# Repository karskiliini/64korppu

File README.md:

# 64korppu

Standardi PC:n 1.44MB 3.5" HD-korppuasema Commodore 64 -tietokoneeseen. FAT12-levyformaatti mahdollistaa tiedostojen siirron C64:n ja PC:n välillä.

## Vaihtoehdot

| # | Ratkaisu | Liitäntä | Hinta | RAM | Tasonmuuntimet | Suositus |
|---|---|---|---|---|---|---|
| **[A](docs/A-IEC-Pico/)** | **IEC + Raspberry Pi Pico** | IEC-sarjaväylä | ~12€ | 264 KB | 4x BSS138 | **Suositeltu** |
| [B](docs/B-Expansion-FDC/) | Expansion port + FDC-piiri | Expansion port | ~20-30€ | - | Ei | Nopein |
| [C](docs/C-Userport-Pico/) | User port + Raspberry Pi Pico | User port | ~12€ | 264 KB | 1x 74LVC245 + 2x BSS138 | Kompromissi |
| [D](docs/D-IEC-Nano/) | IEC + Arduino Nano | IEC-sarjaväylä | ~8€ | 2 KB | **Ei yhtään** | Halvin |
| [E](docs/E-IEC-Nano-SRAM/) | IEC + Arduino Nano + SPI SRAM | IEC-sarjaväylä | ~10-13€ | 2+128 KB | **Ei yhtään** | Nano tehostettuna |

## Arkkitehtuuri

```
C64 ──[IEC / User port / Expansion port]──> Ohjain ──[34-pin]──> PC 3.5" HD floppy
                                                         │
                                                    FAT12-levy
                                                    (1.44 MB)
                                                         │
                                                    PC lukee/kirjoittaa
                                                    samaa levyä
```

## Miksi?

- **Tiedostonsiirto** C64:n ja modernin PC:n välillä ilman erikoislaitteita
- **FAT12** on universaali — levy toimii molemmissa koneissa
- **.PRG-tiedostot** tallennetaan suoraan levylle (2 tavun load address + data)
- **.D64 disk imaget** tuettuja — kopioi .D64-tiedosto levylle, mounttaa C64:llä, lataa ohjelmia suoraan
- C64:llä: `LOAD "PELI.PRG",8` / `SAVE "OMA.PRG",8` / `LOAD "$",8`

## Projektin rakenne

```
64korppu/
├── docs/
│   ├── A-IEC-Pico/           Vaihtoehto A: IEC + Pico (suositeltu)
│   │   ├── README.md         Yhteenveto
│   │   ├── kuvaus.md         Arkkitehtuuri ja komponentit
│   │   ├── piirikaavio.md    Yksityiskohtainen piirikaavio
│   │   └── d64-tuki.md       D64 disk image -tuki
│   ├── B-Expansion-FDC/      Vaihtoehto B: Expansion port + FDC
│   │   ├── README.md
│   │   ├── kuvaus.md
│   │   └── piirikaavio.md
│   ├── C-Userport-Pico/      Vaihtoehto C: User port + Pico
│   │   ├── README.md
│   │   ├── kuvaus.md
│   │   └── piirikaavio.md
│   ├── D-IEC-Nano/           Vaihtoehto D: IEC + Arduino Nano
│   │   ├── README.md
│   │   ├── kuvaus.md
│   │   └── piirikaavio.md
│   └── E-IEC-Nano-SRAM/      Vaihtoehto E: IEC + Nano + 128KB SRAM
│       ├── README.md
│       ├── kuvaus.md
│       └── piirikaavio.md
├── firmware/                  Pico-firmware (vaihtoehto A)
│   ├── CMakeLists.txt
│   ├── include/               Header-tiedostot
│   │   ├── cbm_dos.h          CBM-DOS-emulaatio
│   │   ├── d64.h              D64 disk image -tuki
│   │   ├── fat12.h            FAT12-tiedostojärjestelmä
│   │   ├── floppy_ctrl.h      Floppy-aseman ohjaus
│   │   ├── iec_protocol.h     IEC-väyläprotokolla
│   │   └── mfm_codec.h        MFM-koodaus/dekoodaus
│   ├── src/                   Lähdekoodit
│   │   ├── main.c             Pääohjelma, dual-core, inter-core viestit
│   │   ├── cbm_dos.c          LOAD/SAVE/$, CD:/S:/R:/N:/I:, D64-moodi
│   │   ├── d64.c              D64-parsinta, mount/unmount, BAM, T/S-ketjut
│   │   ├── fat12.c            FAT12 mount/read/write/delete/format
│   │   ├── floppy_ctrl.c      GPIO-ohjaus: moottori, seek, side select
│   │   ├── iec_protocol.c     ATN/CLK/DATA bit-bang, byte send/receive
│   │   └── mfm_codec.c        MFM-dekoodaus, CRC-CCITT, sektorihaku
│   └── pio/                   PIO-ohjelmat (RP2040)
│       ├── iec_bus.pio        IEC-vastaanotto
│       ├── mfm_read.pio       MFM flux-transitioiden mittaus
│       └── mfm_write.pio      MFM flux-transitioiden generointi
└── test/                      Testit (ajetaan host-koneella, ei tarvitse Picoa)
    ├── Makefile               Kääntää testit ja IEC bridge
    ├── test_d64.c             D64-moduulin yksikkötestit (27 testiä)
    ├── mock_fat12.c/h         FAT12-mock: tiedostot muistissa
    ├── gen_test_d64.py        Generoi testi-.D64-imagen
    └── vice/                  IEC bridge integraatiotestaukseen
        ├── iec_bridge.c       TCP-palvelin: oikea CBM-DOS + D64 host-koneella
        ├── mock_iec.c/h       IEC-protokollan stubit
        ├── vice_test.py       Python-testiskripti (simuloi C64 IEC-komentoja)
        └── README.md          Bridge-arkkitehtuuri ja ohje
```

## Testaus

Kolme tasoa, kaikki ajettavissa ilman laitteistoa (Linux/macOS):

**1. Host-yksikkötestit** — D64, CBMFS, FAT12, fastload, LZ4, MFM:

```bash
cd test
make test          # kaikki testisarjat (mm. test_mfm_decode: firmiksen
                   # oikea MFM-dekoodauskoodi synteettistä HD-raitaa
                   # vasten — jitter, moottorin nopeusvirhe, CRC-viat)
```

**2. SimAVR-emulaatio** — aito käännetty `floppy_reader.elf` ajetaan
syklitarkasti virtuaalisen korppuaseman ja SPI-SRAMin kanssa; MFM-
signaali syötetään ICP1-pinniin ja dekoodattu sektori verifioidaan
tavulleen AVR:n RAMista:

```bash
cd tools/sim
make test          # skenaariomatriisi: nominal, 23LC256, moottori
                   # ±1.5%, jitteri ±125ns — PASS/FAIL per skenaario
```

**3. VICE IEC bridge** — CBM-DOS + D64 integraatio:

```bash
cd test
make               # kääntää myös IEC bridge
./vice/iec_bridge  # käynnistä TCP-palvelin
python3 vice/vice_test.py  # aja integraatiotestit toisessa terminaalissa
```

## Tila

Projekti on suunnitteluvaiheessa. Firmware-koodi on kirjoitettu vaihtoehto A:lle (Pico), mutta ei vielä testattu oikealla laitteistolla. D64 disk image -tuki toteutettu ja testattu host-tasolla.

## Lisenssi

Avoin lähdekoodi. Lisenssi lisätään myöhemmin.

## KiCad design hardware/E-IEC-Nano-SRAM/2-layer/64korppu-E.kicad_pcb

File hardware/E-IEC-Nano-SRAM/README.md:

# 64korppu-E — Hardware

> Arduino Nano + 23LC256 SPI SRAM + 74HC595

## 4-layer (70x60mm)

## 2-layer (140x120mm)

## Variantit

| Kansio | Kerrokset | Mitat (mm) | Pinta-ala |
|--------|-----------|------------|-----------|
| [2-layer/](2-layer/) | F.Cu + B.Cu | 140.0 × 120.0 | 16 800 mm² |
| [4-layer/](4-layer/) | F.Cu / GND / +5V / B.Cu | 70.0 × 60.0 | 4 200 mm² |

## Dokumentaatio

Katso [docs/E-IEC-Nano-SRAM/](../../docs/E-IEC-Nano-SRAM/) — piirikaavio, diagnostiikkapadit, komponenttikuvaus.

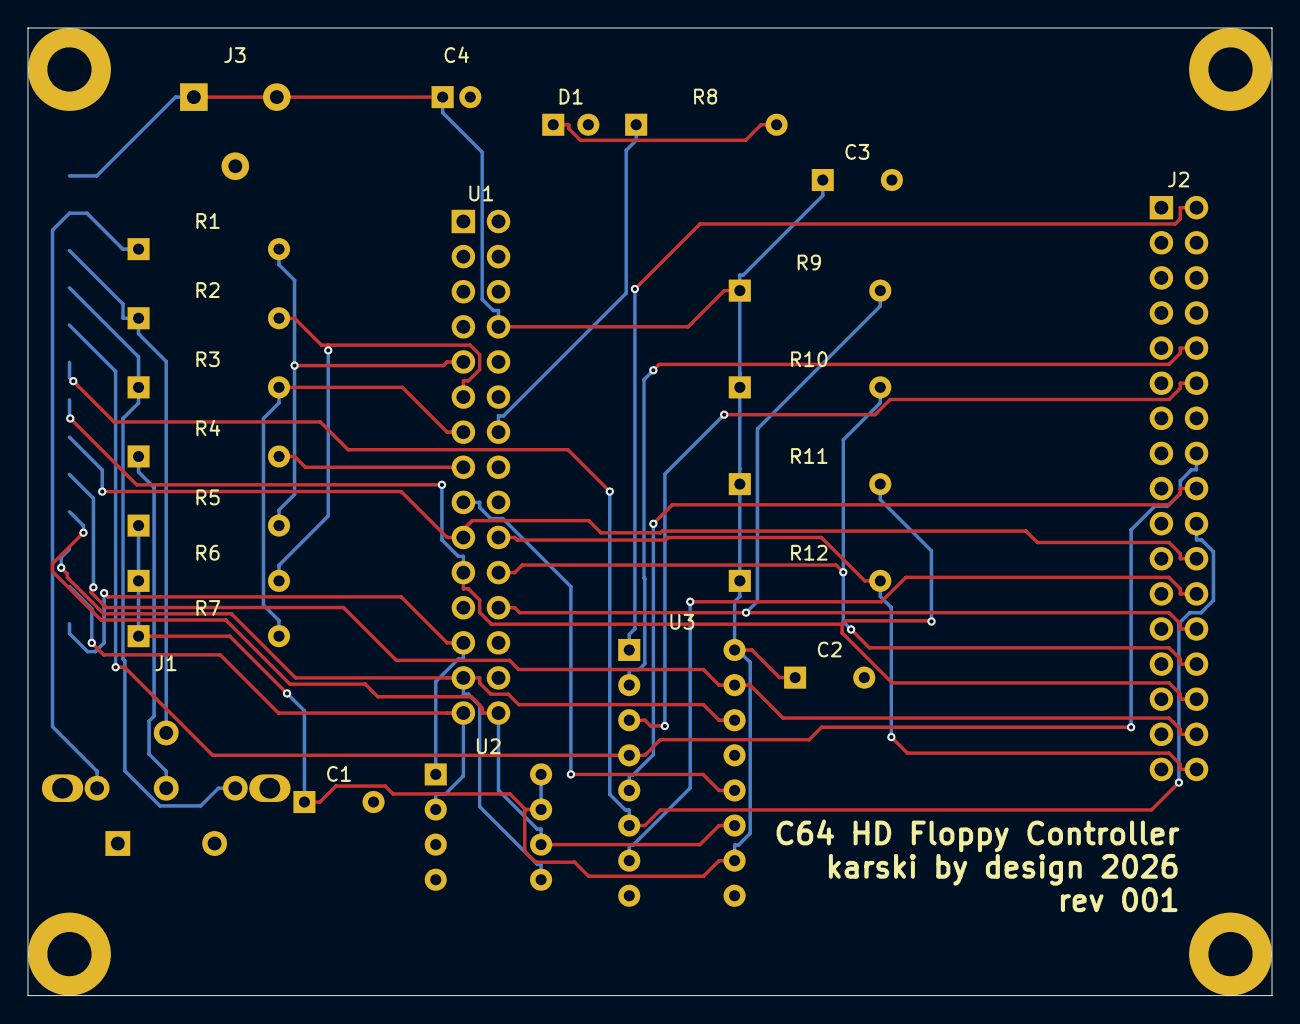
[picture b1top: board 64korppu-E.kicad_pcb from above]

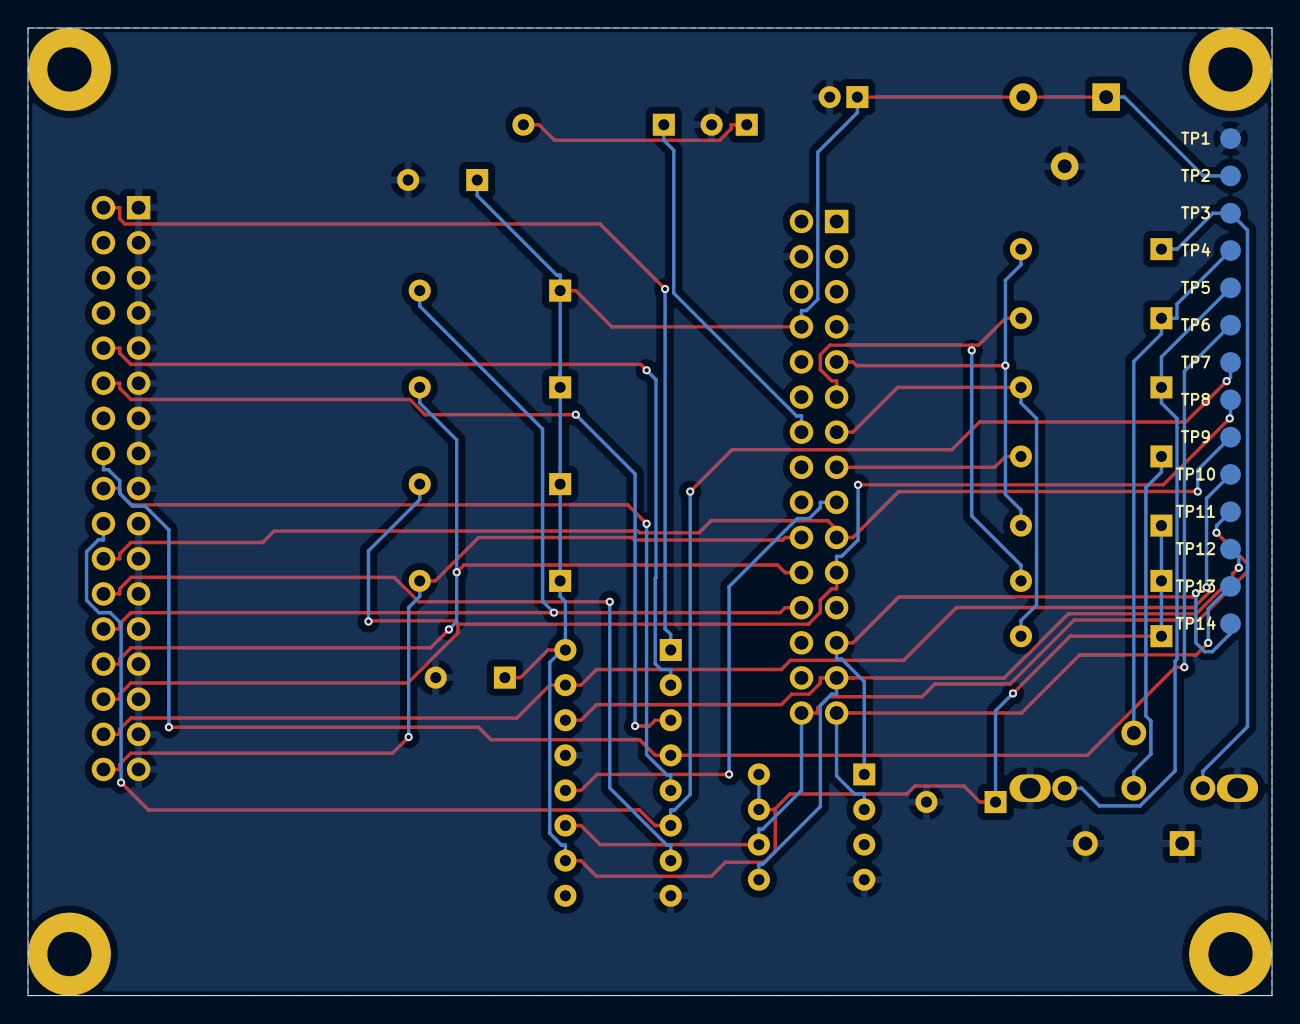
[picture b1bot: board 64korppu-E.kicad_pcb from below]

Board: 2 copper layers, 90.0 x 70.0 mm, 41 parts (14 on the bottom side), 30 nets.

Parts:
C1, C2, C3: 100nF; C_Disc_D5.0mm_W2.5mm_P5.00mm
C4: 100uF; CP_Radial_D5.0mm_P2.00mm
D1: LED; LED_D3.0mm
H1, H2, H3, H4: MountingHole; MountingHole_3.2mm_M3
J1: DIN-6_IEC; DIN-6_IEC_Vertical
J2: Floppy_34pin; IDC-Header_2x17_P2.54mm_Vertical
J3: DC_Jack; BarrelJack_Horizontal
R1, R2, R3, R4: 1k; R_Axial_DIN0207_L6.3mm_D2.5mm_P10.16mm_Horizontal
R5, R6, R7: 4.7k; R_Axial_DIN0207_L6.3mm_D2.5mm_P10.16mm_Horizontal
R8: 330; R_Axial_DIN0207_L6.3mm_D2.5mm_P10.16mm_Horizontal
R9, R10, R11, R12: 10k; R_Axial_DIN0207_L6.3mm_D2.5mm_P10.16mm_Horizontal
TP1: GND; TestPoint_Pad_D1.5_SMD
TP2: +5V; TestPoint_Pad_D1.5_SMD
TP3: IEC_ATN; TestPoint_Pad_D1.5_SMD
TP4: IEC_CLK; TestPoint_Pad_D1.5_SMD
TP5: IEC_DATA; TestPoint_Pad_D1.5_SMD
TP6: FLOPPY_MOTOR; TestPoint_Pad_D1.5_SMD
TP7: FLOPPY_STEP; TestPoint_Pad_D1.5_SMD
TP8: FLOPPY_RDATA; TestPoint_Pad_D1.5_SMD
TP9: FLOPPY_WDATA; TestPoint_Pad_D1.5_SMD
TP10: FLOPPY_SIDE1; TestPoint_Pad_D1.5_SMD
TP11: SPI_SCK; TestPoint_Pad_D1.5_SMD
TP12: SPI_MOSI; TestPoint_Pad_D1.5_SMD
TP13: SPI_MISO; TestPoint_Pad_D1.5_SMD
TP14: SPI_CS_SRAM; TestPoint_Pad_D1.5_SMD
U1: Arduino_Nano; PinHeader_2x15_P2.54mm_Vertical
U2: 23LC256; DIP-8_W7.62mm_Socket
U3: 74HC595; DIP-16_W7.62mm_Socket

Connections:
+5V: C1.1, C2.1, C3.1, C4.1, J3.1, J3.2, R5.1, R6.1, R7.1, R9.1, R10.1, R11.1, R12.1, TP2.1, U1.8, U2.7, U2.8, U3.10, U3.16
FLOPPY_DENSITY: J2.2, U3.1
FLOPPY_DIR: J2.18, U3.5
FLOPPY_DRVSEL: J2.12, U3.3
FLOPPY_DSKCHG: J2.34, R12.2, U1.20
FLOPPY_MOTEA: J2.10, U3.2
FLOPPY_MOTOR: J2.16, TP6.1, U3.4
FLOPPY_RDATA: J2.30, R11.2, TP8.1, U1.21
FLOPPY_SIDE1: J2.32, TP10.1, U3.15
FLOPPY_STEP: J2.20, TP7.1, U3.6
FLOPPY_TRK00: J2.26, R9.2, U1.24
FLOPPY_WDATA: J2.22, TP9.1, U1.19
FLOPPY_WGATE: J2.24, U3.7
FLOPPY_WPT: J2.28, R10.2, U1.22
GND: C1.2, C2.2, C3.2, C4.2, D1.2, J1.1, J1.2, J1.SH, J2.1, J2.3, J2.5, J2.7, J2.9, J2.11, J2.13, J2.15, J2.17, J2.19, J2.21, J2.23, J2.25, J2.27, J2.29, J2.31, J2.33, J3.3, TP1.1, U1.4, U1.7, U2.4, U3.8, U3.13
IEC_ATN: J1.3, R1.1, TP3.1
IEC_CLK: J1.4, R2.1, TP4.1
IEC_DATA: J1.5, R3.1, TP5.1
IEC_RESET: J1.6, R4.1
LATCH_595: U1.17, U3.12
LED_ANODE: R8.1, U1.14
LED_CATHODE: D1.1, R8.2
NANO_D2: R1.2, R5.2, U1.9
NANO_D3: R2.2, R6.2, U1.11
NANO_D4: R3.2, R7.2, U1.13
NANO_D5: R4.2, U1.15
SPI_CS_SRAM: TP14.1, U1.25, U2.1
SPI_MISO: TP13.1, U1.29, U2.2
SPI_MOSI: TP12.1, U1.27, U2.5, U3.14
SPI_SCK: TP11.1, U1.30, U2.6, U3.11

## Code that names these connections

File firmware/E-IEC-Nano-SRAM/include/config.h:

#ifndef CONFIG_H
#define CONFIG_H

#include <stdint.h>
#include <stdbool.h>

/*
 * Hardware configuration for Alternative E:
 * Arduino Nano (ATmega328P) + 23LC512 SPI SRAM + 74HC595 shift register
 */

/* --- SRAM Memory Map (23LC512, 64KB) --- */

#define SRAM_SIZE           0x10000UL   /* 65536 bytes */

#define SRAM_MFM_TRACK      0x00000UL   /* MFM decoded track buffer */
#define SRAM_MFM_TRACK_SIZE 12496

/* Raw capture buffer: stores uint8_t timer intervals during polled capture.
 * Occupies entire SRAM during capture (other buffers not needed then).
 * HD 500kbps: ~74000 flux-transitiota/kierros (keskiväli ~2.7µs), joten
 * 50000 intervallia ≈ 0.7 kierrosta. Retry-silmukka kattaa loput.
 * HUOM: rajataan ajonaikaisesti sram_capacity():n mukaan — 23LC256
 * (32KB) kiertäisi muuten ympäri ja korruptoisi capturen. */
#define SRAM_RAW_CAPTURE      0x00000UL
#define SRAM_RAW_CAPTURE_SIZE 50000U

#define SRAM_FAT_CACHE      0x030D0UL   /* FAT table cache (9 sectors) */
#define SRAM_FAT_CACHE_SIZE 4608        /* 9 * 512 */

#define SRAM_SECTOR_BUF1    0x042D0UL   /* Sector buffer #1 */
#define SRAM_SECTOR_BUF2    0x044D0UL   /* Sector buffer #2 */
#define SRAM_SECTOR_SIZE    512

#define SRAM_DIR_BUF        0x046D0UL   /* Directory listing buffer */
#define SRAM_DIR_BUF_SIZE   4096

#define SRAM_IEC_BUF        0x056D0UL   /* IEC channel buffer */
#define SRAM_IEC_BUF_SIZE   512

/* LZ4 compression buffers (in external SRAM, not internal RAM) */
#define SRAM_COMP_RAW       0x058D0UL   /* Raw data before compression */
#define SRAM_COMP_RAW_SIZE  128         /* = COMPRESS_BLOCK_SIZE */
#define SRAM_COMP_FRAME     0x05AD0UL   /* Framed LZ4 output */
#define SRAM_COMP_FRAME_SIZE 172        /* = COMPRESS_FRAME_BUF_SIZE */
                                        /* Vapaa: 0x05B7C - 0x0FFFF = ~41.5 KB */

/* --- Floppy Geometry --- */

#define FLOPPY_TRACKS         80
#define FLOPPY_SIDES           2
#define FLOPPY_SECTORS_HD     18
#define FLOPPY_SECTOR_SIZE   512
#define FLOPPY_TOTAL_SECTORS (FLOPPY_TRACKS * FLOPPY_SIDES * FLOPPY_SECTORS_HD)

/* Timing constants (microseconds) */
#define FLOPPY_STEP_PULSE_US    3
#define FLOPPY_STEP_SETTLE_MS  15
#define FLOPPY_STEP_RATE_MS     3

/* Error codes */
#define FLOPPY_OK               0
#define FLOPPY_ERR_NO_TRK0    -1
#define FLOPPY_ERR_SEEK        -2
#define FLOPPY_ERR_READ        -3
#define FLOPPY_ERR_WRITE       -4
#define FLOPPY_ERR_WP          -5
#define FLOPPY_ERR_NO_DISK     -6
#define FLOPPY_ERR_CRC         -7
#define FLOPPY_ERR_NO_SECTOR   -8
#define FLOPPY_ERR_TIMEOUT     -9

/* --- AVR-specific Pin Assignments --- */

#ifdef __AVR__

#include <avr/io.h>

/* IEC bus (direct GPIO, active-low open-collector) */
#define IEC_PIN_ATN      PD2    /* INT0 interrupt */
#define IEC_PIN_CLK      PD3
#define IEC_PIN_DATA     PD4
#define IEC_PIN_RESET    PD5
#define IEC_DDR          DDRD
#define IEC_PORT         PORTD
#define IEC_PINR         PIND

/* SPI (shared SRAM + 74HC595) */
#define SPI_CS_SRAM      PB2    /* D10 = /CS_SRAM */
#define SPI_MOSI         PB3    /* D11 */
#define SPI_MISO         PB4    /* D12 */
#define SPI_SCK          PB5    /* D13 */

/* 74HC595 latch */
#define SR_RCLK_PIN      PD6    /* D6 = RCLK (latch) */
#define SR_RCLK_DDR      DDRD
#define SR_RCLK_PORT     PORTD

/* 74HC595 output enable (active LOW, active = outputs drive) */
#define SR_OE_PIN        PC3    /* A3 = /OE */
#define SR_OE_DDR        DDRC
#define SR_OE_PORT       PORTC

/* Floppy direct GPIO */
#define FLOPPY_WDATA_PIN    PD7    /* D7 = /WDATA (direct for timing) */
#define FLOPPY_WDATA_DDR    DDRD
#define FLOPPY_WDATA_PORT   PORTD
#define FLOPPY_RDATA_PIN    PB0    /* D8 = /RDATA (ICP1 input capture) */
#define FLOPPY_LED_PIN      PB1    /* D9 = LED */

/* Floppy input (active-low, internal pull-up) */
#define FLOPPY_TRK00_PIN    PC0    /* A0 = /TRK00 */
#define FLOPPY_WPT_PIN      PC1    /* A1 = /WPT */
#define FLOPPY_DSKCHG_PIN   PC2    /* A2 = /DSKCHG */
#define FLOPPY_IN_DDR       DDRC
#define FLOPPY_IN_PORT      PORTC
#define FLOPPY_IN_PINR      PINC

#endif /* __AVR__ */

/* --- 74HC595 Shift Register Bit Assignments --- */

#define SR_BIT_SIDE1     0    /* QA (pin 15) = /SIDE1 */
#define SR_BIT_DENSITY   1    /* QB (pin  1) = /DENSITY */
#define SR_BIT_MOTEA     2    /* QC (pin  2) = /MOTEA */
#define SR_BIT_DRVSEL    3    /* QD (pin  3) = /DRVSEL */
#define SR_BIT_MOTOR     4    /* QE (pin  4) = /MOTOR */
#define SR_BIT_DIR       5    /* QF (pin  5) = /DIR */
#define SR_BIT_STEP      6    /* QG (pin  6) = /STEP */
#define SR_BIT_WGATE     7    /* QH (pin  7) = /WGATE */

/* Default: all deasserted (HIGH for active-low signals) */
#define SR_DEFAULT       0xFF

/* --- IEC Protocol --- */

#define IEC_DEFAULT_DEVICE   8
#define IEC_NUM_CHANNELS    16

/* IEC bus commands (under ATN) */
#define IEC_CMD_LISTEN      0x20
#define IEC_CMD_UNLISTEN    0x3F
#define IEC_CMD_TALK        0x40
#define IEC_CMD_UNTALK      0x5F
#define IEC_CMD_SECOND      0x60    /* 0x60-0x6F: data channel select (SA) */
#define IEC_CMD_CLOSE       0xE0    /* 0xE0-0xEF: CLOSE + SA */
#define IEC_CMD_OPEN        0xF0    /* 0xF0-0xFF: OPEN + SA (filename follows) */

/* Secondary addresses */
#define IEC_SA_LOAD          0
#define IEC_SA_SAVE          1
#define IEC_SA_COMMAND      15

/* Timing (microseconds) */
#define IEC_TIMING_LISTENER_HOLD    80
#define IEC_TIMING_TALKER_SETUP     80
#define IEC_TIMING_CLK_LOW          60
#define IEC_TIMING_CLK_HIGH         60
#define IEC_TIMING_EOI_TIMEOUT     200
#define IEC_TIMING_EOI_ACK          60
#define IEC_TIMING_BETWEEN_BYTES   100
#define IEC_TIMEOUT_US           10000

/* --- MFM Codec --- */

/*
 * HD 500 kbit/s MFM: databitti = 2µs, puolisolu (T) = 1µs = 16 tikkiä.
 * Flux-transitioiden välit ovat 2T/3T/4T = 2/3/4 µs = 32/48/64 tikkiä
 * (16MHz Timer1, ei prescaleria).
 *
 * Kirjoituspuoli: wait_bit_cell() odottaa yhden puolisolun (16 tikkiä)
 * ja sitä kutsutaan kahdesti per databitti → 2µs/bitti = 500 kbit/s.
 *
 * HUOM: aiempi versio oletti 2T=64 tikkiä (4µs) — se on DD 250 kbit/s
 * -ajoitus, ei HD. Mitatut "klusterit" ~107/133/155 tikkiä olivat
 * ISR-pohjaisen capturen oman palveluajan artefakteja, eivät levyn
 * signaalia (ks. mfm_codec.c: polled capture).
 */
#define MFM_TICKS_PER_CELL_HD    16
/*
 * Pulse classification thresholds (Timer1 ticks at 16MHz).
 * Nominaalit 32/48/64; rajat klusterien puolivälissä. Kalibrointi
 * (mfm_calibrate) säätää nämä mitatuista klustereista ajon aikana.
 */
#define MFM_THRESHOLD_SHORT     40    /* < 40: 2T */
#define MFM_THRESHOLD_MEDIUM    56    /* < 56: 3T */
#define MFM_THRESHOLD_LONG      76    /* < 76: 4T, muuten virhe */

/* MFM address marks */
#define MFM_SYNC_BYTE   0xA1
#define MFM_IDAM        0xFE
#define MFM_DAM         0xFB
#define MFM_CRC_INIT    0xFFFF
#define MFM_CRC_POLY    0x1021

/* --- LZ4 Compression --- */

/*
 * COMPRESS_BLOCK_SIZE: raakadatan lohkokoko tavuina.
 * Suurempi lohko = parempi pakkaus, mutta enemmän RAMia:
 *
 *   Lohko   raw_buf   frame_buf   hash (pino)   Yhteensä   Pakkaus
 *   ─────   ───────   ─────────   ───────────   ────────   ───────
 *    64B      64B       100B       128B (64×2)    292B      ~1.3:1
 *   128B     128B       172B       256B (128×2)   556B      ~1.5:1
 *   256B     256B       300B       512B (256×2)  1068B      ~1.8:1
 *
 * 23LC512:n 64KB SRAM:issa raakadata- ja kehyspuskurit ovat
 * ulkoisessa muistissa (SRAM_COMP_RAW / SRAM_COMP_FRAME).
 * Hash-taulu (COMPRESS_HASH_SIZE × 2 tavua) on pinossa
 * kompression aikana: 256 × 2 = 512 tavua.
 *
 * Lohkokoko 128B: pakkauspolun hetkellinen pinonkulutus on
 * raw(128) + frame(172) + hash(256) ≈ 556B. Aiempi 512B lohko vaati
 * ~1.6KB pinoa, mikä ei mahdu ATmega328P:n 2KB RAMiin staattisen
 * datan (~1.1KB) rinnalle → pinovuoto. Kehysformaatissa on raw_size-
 * kenttä, joten lohkokoon muutos ei riko purkupuolta.
 *
 * COMPRESS_HASH_SIZE = hash-taulun entrymäärä (2 tavua/entry pinossa),
 * pitää olla 2:n potenssi ja ≤ 256 (lz4_hash palauttaa uint8_t).
 *
 * COMPRESS_FRAME_BUF_SIZE = 4 (header) + BLOCK_SIZE + BLOCK_SIZE/255 + 16
 * (worst case: ei-pakattava data + LZ4 token overhead).
 */
#define COMPRESS_BLOCK_SIZE     128
#define COMPRESS_HASH_SIZE      128
#define COMPRESS_FRAME_BUF_SIZE 172

#endif /* CONFIG_H */

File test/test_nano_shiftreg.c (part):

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 *
 * Verifies that firmware SR_BIT_* constants match the hardware:
 *   74HC595 DIP-16 pinout (from KiCad schematic):
 *     Pin 15 (QA, bit 0) → FLOPPY_SIDE1
 *     Pin  1 (QB, bit 1) → FLOPPY_DENSITY
 *     Pin  2 (QC, bit 2) → FLOPPY_MOTEA
 *     Pin  3 (QD, bit 3) → FLOPPY_DRVSEL
 *     Pin  4 (QE, bit 4) → FLOPPY_MOTOR
 *     Pin  5 (QF, bit 5) → FLOPPY_DIR
 *     Pin  6 (QG, bit 6) → FLOPPY_STEP
 *     Pin  7 (QH, bit 7) → FLOPPY_WGATE
 *
 * These tests would have caught the off-by-one bit mapping bug where
 * all signals were shifted by one position.
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 * 74HC595 data sheet: SPI shifts MSB first.
 * QH gets bit 7 (first shifted in), QA gets bit 0 (last shifted in).
 * Hardware pinout (from KiCad PCB U3 pad→net):
 *   QA (pin 15) = FLOPPY_SIDE1    → must be bit 0
 *   QB (pin  1) = FLOPPY_DENSITY  → must be bit 1
 *   QC (pin  2) = FLOPPY_MOTEA   → must be bit 2
 *   QD (pin  3) = FLOPPY_DRVSEL  → must be bit 3
 *   QE (pin  4) = FLOPPY_MOTOR   → must be bit 4
 *   QF (pin  5) = FLOPPY_DIR     → must be bit 5
 *   QG (pin  6) = FLOPPY_STEP    → must be bit 6
 *   QH (pin  7) = FLOPPY_WGATE   → must be bit 7
 */

TEST(side1_is_bit_0_qa)
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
